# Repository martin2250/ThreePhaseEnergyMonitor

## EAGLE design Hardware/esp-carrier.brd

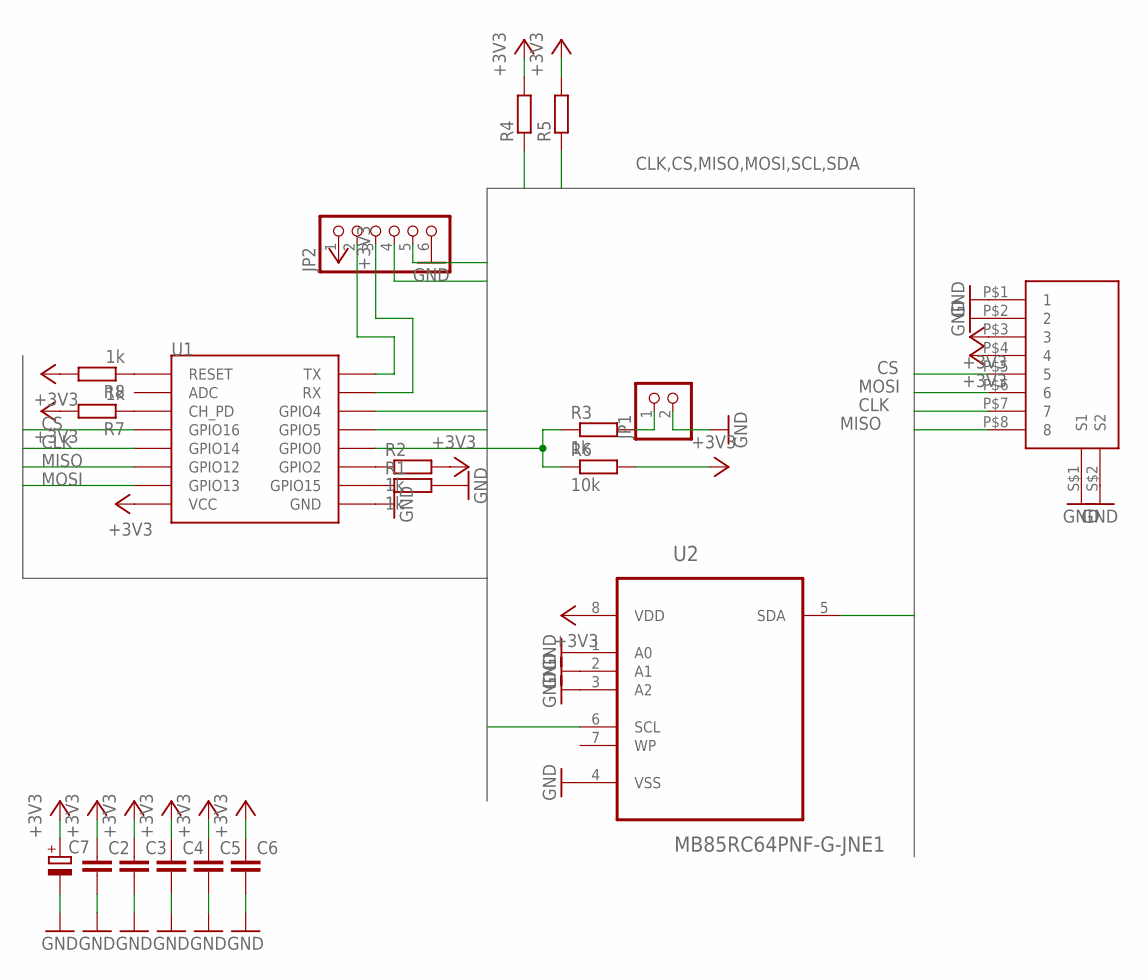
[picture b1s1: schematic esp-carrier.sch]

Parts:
C1: RJ45-ASSMANN
C2, C3, C4, C5, C6: C-EUC0805; C0805
C7: CPOL-EUF; PANASONIC_F
JP1: PINHD-1X2; 1X02
JP2: PINHD-1X6; 1X06
R1, R2, R3, R7, R8: 1k; R0805
R4, R5: R-EU_R0805; R0805
R6: 10k; R0805
U1: ESP12SMD; ESP12-SMD
U2: MB85RC64PNF-G-JNE1; SOIC127P600X175-8N

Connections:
+3V3: C1.P$3 (3), C1.P$4 (4), C2.1, C3.1, C4.1, C5.1, C6.1, C7.+, JP2.1, R2.2, R4.2, R5.2, R6.2, R7.2, R8.2, U1.VCC, U2.8 (VDD)
CLK: C1.P$7 (7), U1.GPIO14
CS: C1.P$5 (5), U1.GPIO16
GND: C1.P$1 (1), C1.P$2 (2), C1.S$1 (S1), C1.S$2 (S2), C2.2, C3.2, C4.2, C5.2, C6.2, C7.-, JP1.2, JP2.6, R1.2, U1.GND, U2.1 (A0), U2.2 (A1), U2.3 (A2), U2.4 (VSS)
MISO: C1.P$8 (8), U1.GPIO12
MOSI: C1.P$6 (6), U1.GPIO13
unnamed: R1.1, U1.GPIO15
unnamed: R2.1, U1.GPIO2
unnamed: R3.1, R6.1, U1.GPIO0
unnamed: JP1.1, R3.2
unnamed: JP2.2, U1.TXD0 (TX)
unnamed: R7.1, U1.CH_PD
unnamed: JP2.3, U1.RXD0 (RX)
unnamed: R8.1, U1.RESET
SCL: JP2.5, R4.1, U1.GPIO5, U2.6 (SCL)
SDA: JP2.4, R5.1, U1.GPIO4, U2.5 (SDA)

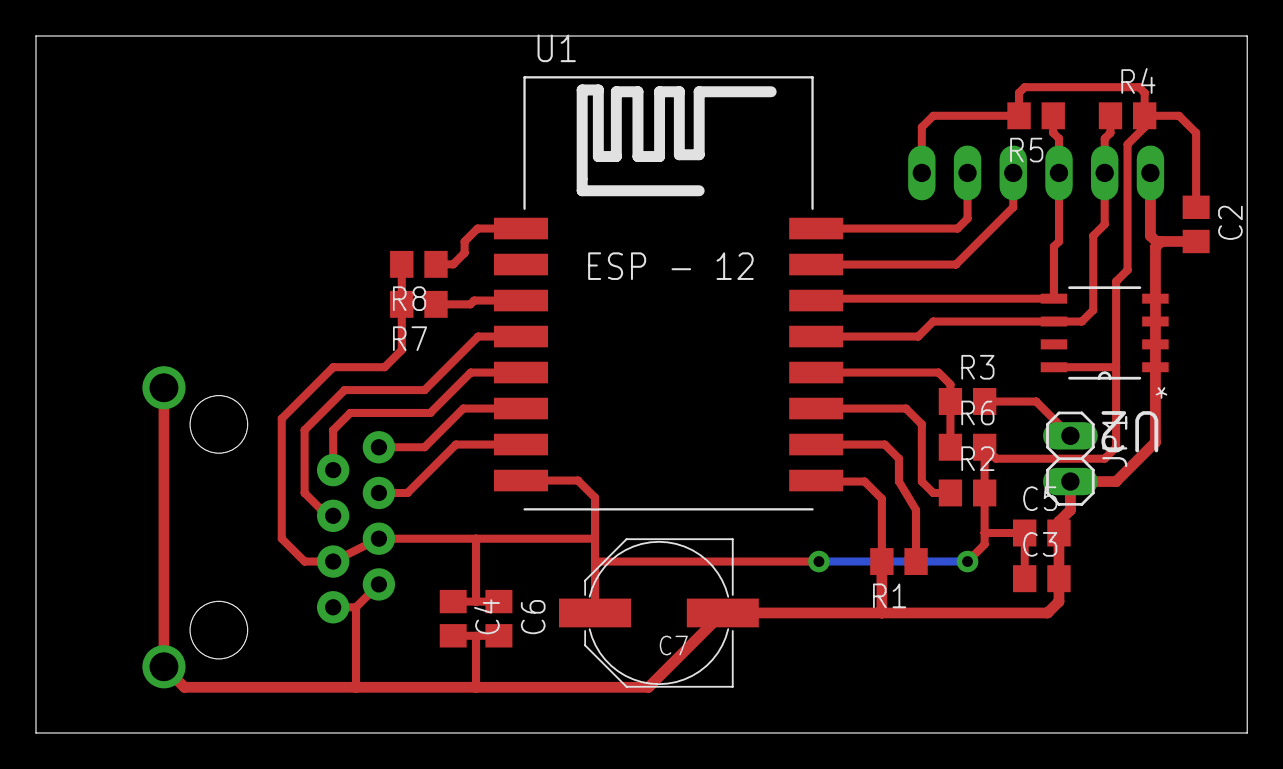
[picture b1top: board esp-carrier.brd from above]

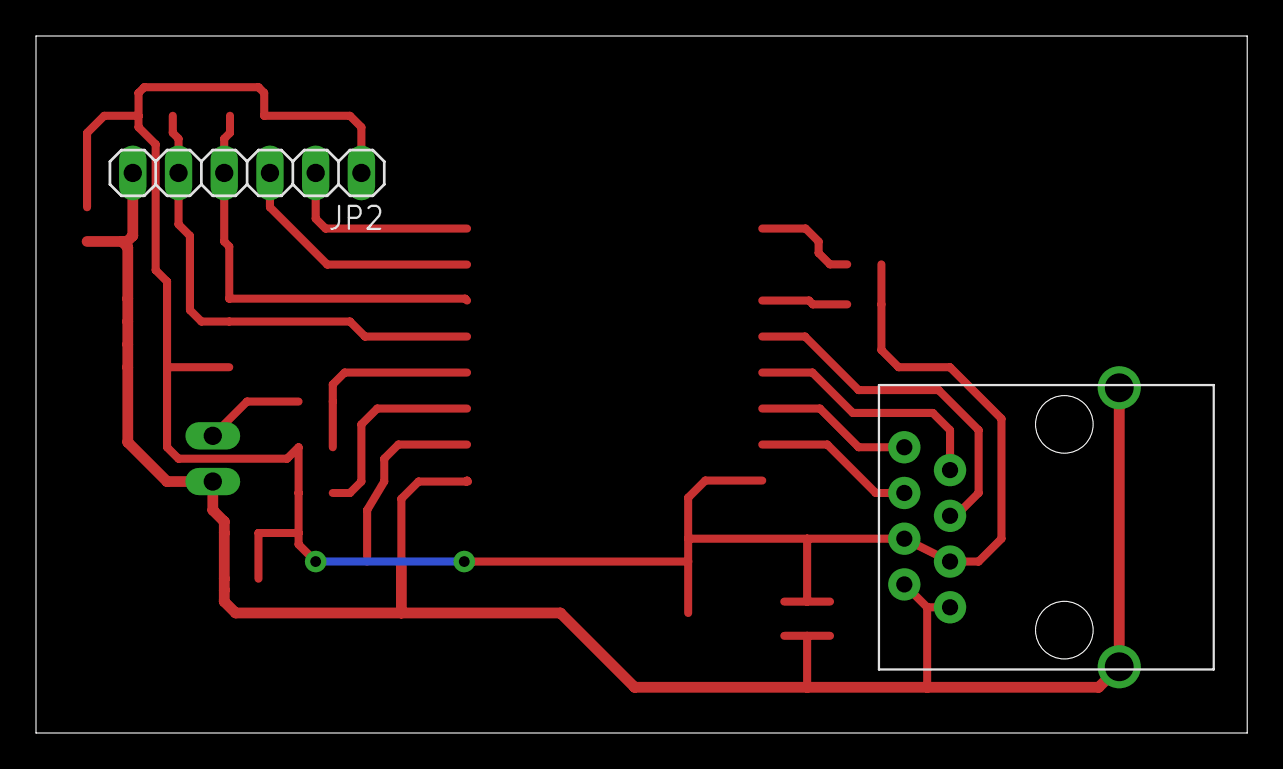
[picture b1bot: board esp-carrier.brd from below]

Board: 2 copper layers, 67.3 x 38.7 mm, 19 parts (2 on the bottom side), 16 nets.

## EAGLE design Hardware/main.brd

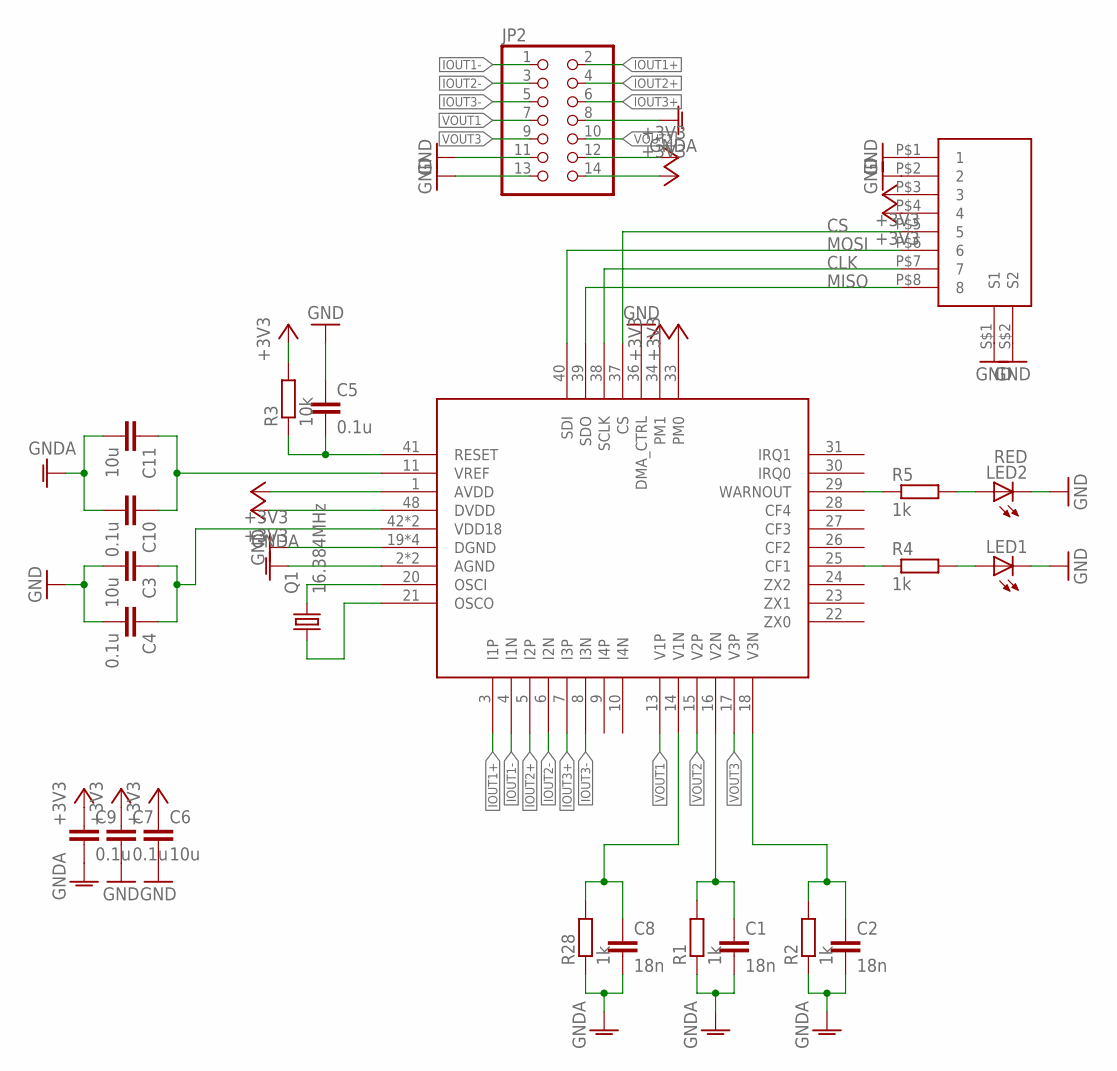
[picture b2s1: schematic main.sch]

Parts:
C1, C2, C8: 18n; C0805
C3, C6: 10u; C1206
C4, C5, C7, C9, C10: 0.1u; C0805
C11: 10u; C0805
C12: RJ45-ASSMANN
JP2: PINHD-2X7; 2X07
LED1: LEDCHIPLED_1206; CHIPLED_1206
LED2: RED; CHIPLED_1206
Q1: 16.384MHz; 5.0X3.2_KX-9A
R1, R2, R28: 1k; M0805
R3: 10k; M0805
R4, R5: 1k; R0805
U$1: ATM90E36A; QFP50P900X900X120-48

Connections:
+3V3: C6.1, C7.1, C9.1, C12.P$3 (3), C12.P$4 (4), JP2.12, JP2.14, R3.2, U$1.1 (AVDD), U$1.33 (PM0), U$1.34 (PM1), U$1.48 (DVDD)
CLK: C12.P$7 (7), U$1.38 (SCLK)
CS: C12.P$5 (5), U$1.37 (CS)
GND: C3.2, C4.2, C5.1, C6.2, C7.2, C12.P$1 (1), C12.P$2 (2), C12.S$1 (S1), C12.S$2 (S2), JP2.11, JP2.13, LED1.C, LED2.C, U$1.19 (DGND), U$1.32 (DGND), U$1.36 (DMA_CTRL), U$1.44 (DGND), U$1.47 (DGND)
GNDA: C1.2, C2.2, C8.2, C9.2, C10.2, C11.2, JP2.8, R1.1, R2.1, R28.1, U$1.2 (AGND), U$1.12 (AGND)
IOUT1+: JP2.2, U$1.3 (I1P)
IOUT1-: JP2.1, U$1.4 (I1N)
IOUT2+: JP2.4, U$1.5 (I2P)
IOUT2-: JP2.3, U$1.6 (I2N)
IOUT3+: JP2.6, U$1.7 (I3P)
IOUT3-: JP2.5, U$1.8 (I3N)
MISO: C12.P$8 (8), U$1.39 (SDO)
MOSI: C12.P$6 (6), U$1.40 (SDI)
unnamed: Q1.3 (2), U$1.20 (OSCI)
unnamed: Q1.1, U$1.21 (OSCO)
unnamed: C5.2, R3.1, U$1.41 (RESET)
unnamed: C3.1, C4.1, U$1.42 (VDD18), U$1.43 (VDD18)
unnamed: R4.1, U$1.25 (CF1)
unnamed: LED1.A, R4.2
unnamed: R5.1, U$1.29 (WARNOUT)
unnamed: LED2.A, R5.2
VOUT1: JP2.7, U$1.13 (V1P)
VOUT2: JP2.10, U$1.15 (V2P)
VOUT3: JP2.9, U$1.17 (V3P)
VOUT4: C8.1, R28.2, U$1.14 (V1N)
VOUT5: C1.1, R1.2, U$1.16 (V2N)
VOUT6: C2.1, R2.2, U$1.18 (V3N)
VREF: C10.1, C11.1, U$1.11 (VREF)

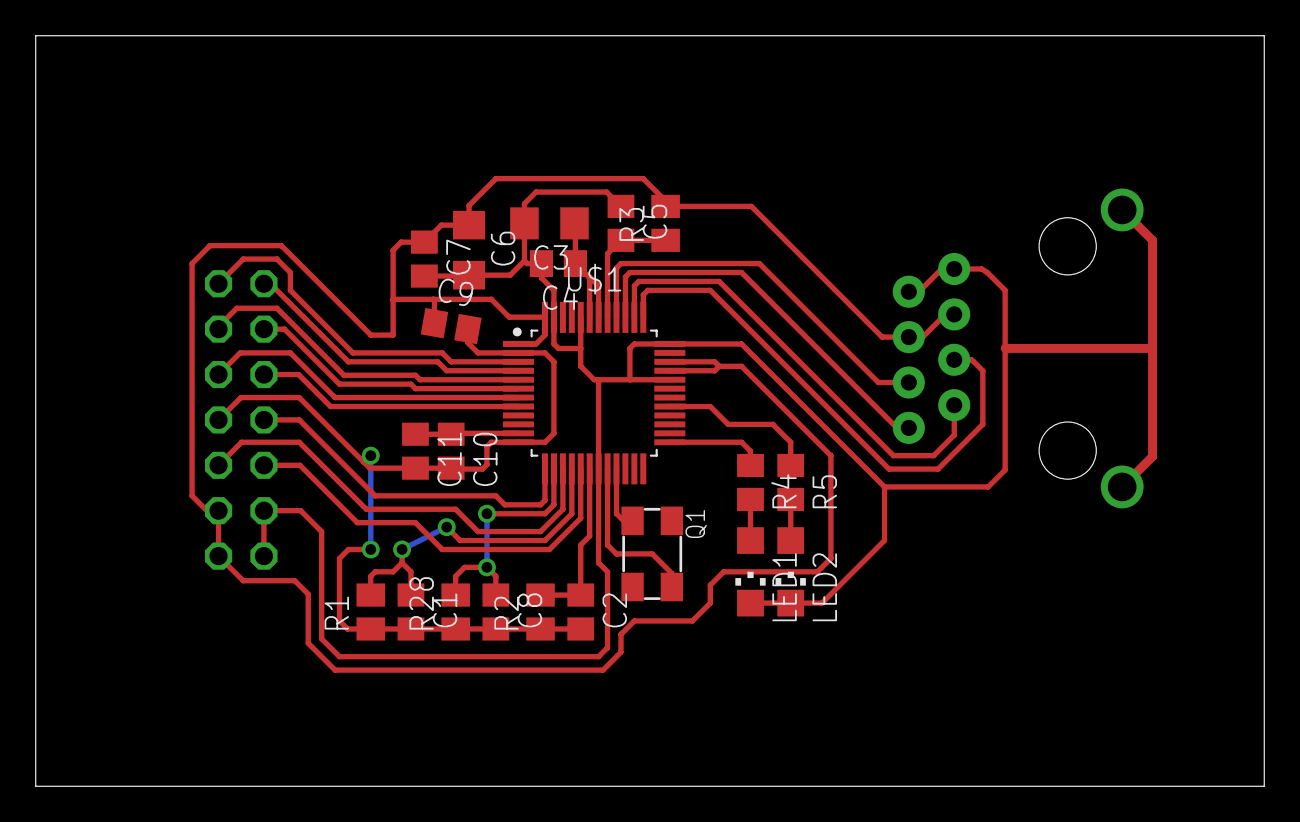
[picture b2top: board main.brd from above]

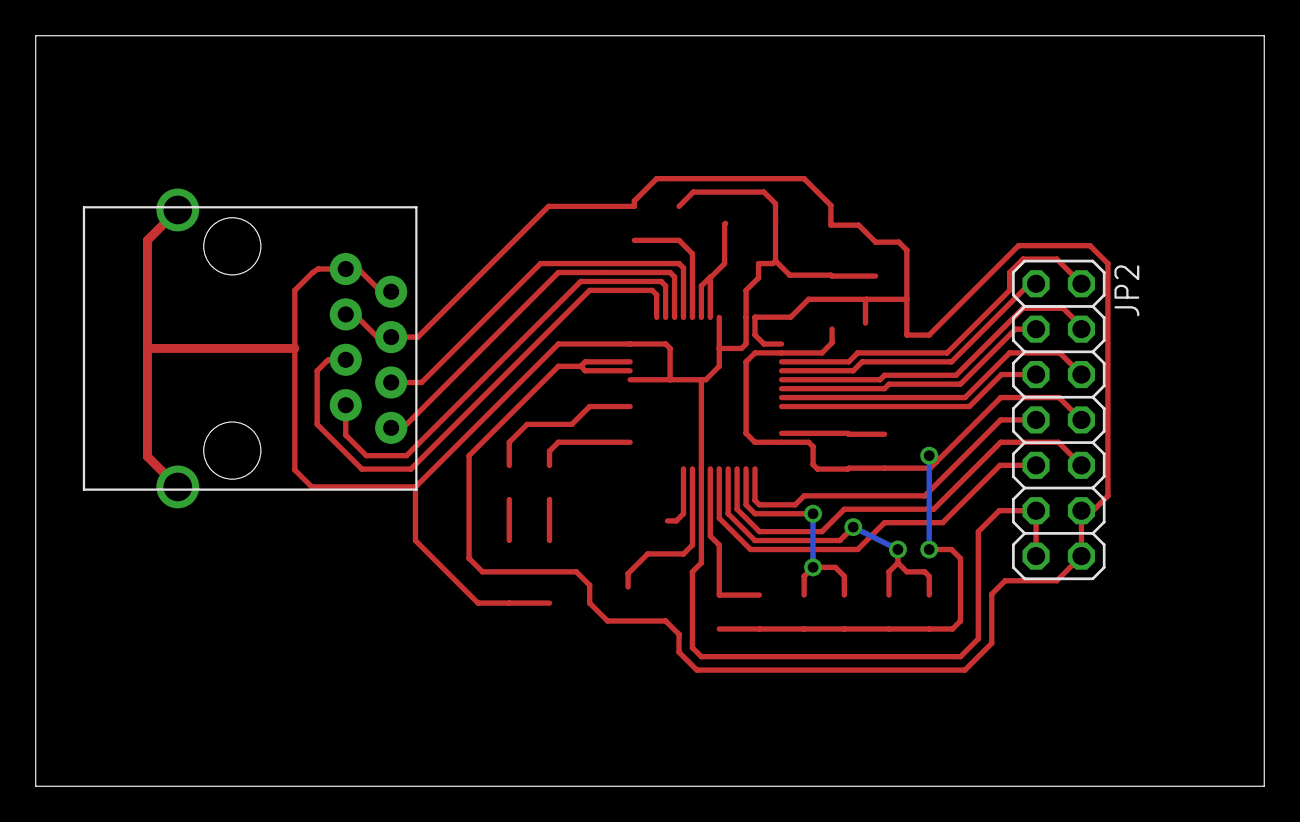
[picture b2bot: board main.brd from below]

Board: 2 copper layers, 68.8 x 42.0 mm, 23 parts (2 on the bottom side), 28 nets.

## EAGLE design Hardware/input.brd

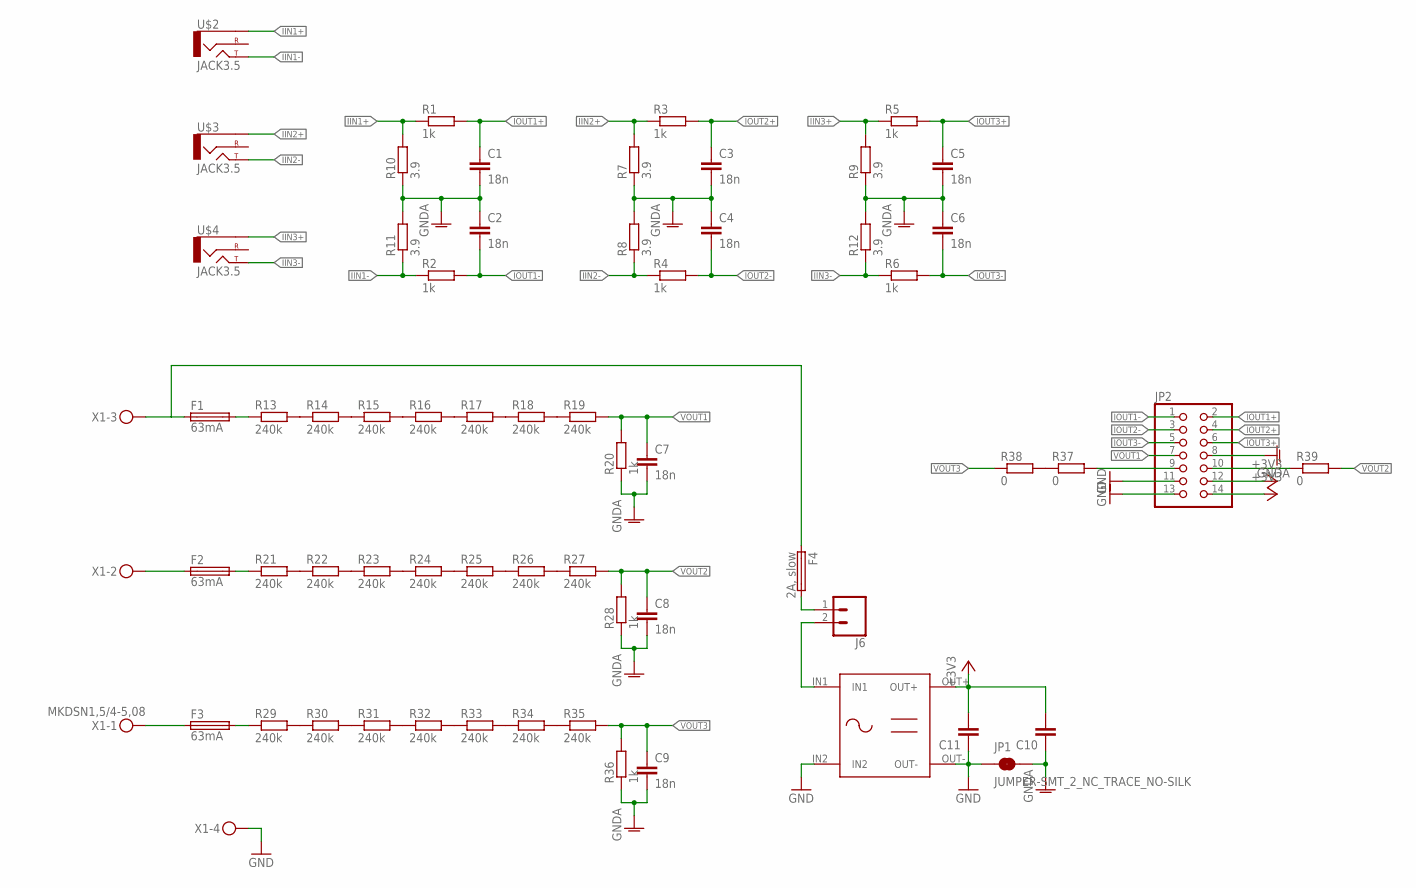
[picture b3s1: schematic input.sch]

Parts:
C1, C2, C3, C4, C5, C6, C7, C8, C9: 18n; C0805
C10, C11: C-EUC1206; C1206
F1, F2, F3: 63mA; SH25
F4: 2A, slow; SH25
J6: CONN_025MM; SCREWTERMINAL-5MM-2
JP1: JUMPER-SMT_2_NC_TRACE_NO-SILK; SMT-JUMPER_2_NC_TRACE_NO-SILK
JP2: PINHD-2X7; 2X07
R1, R2, R3, R4, R5, R6, R20, R28, R36: 1k; M0805
R7, R8, R9, R10, R11, R12: 3.9; M0805
R13, R14, R15, R16, R17, R18, R19, R21, R22, R23, R24, R25, R26, R27, R29, R30, R31, R32, R33, R34, R35: 240k; R1206
R37, R38, R39: 0; R1206
U$1: MW-IRM; MW-IRM-DIP
U$2, U$3, U$4: JACK3.5; AUDIO-JACK
X1: MKDSN1,5/4-5,08

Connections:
+3V3: C10.2, C11.2, JP2.12, JP2.14, U$1.OUT+
GND: C11.1, JP1.1, JP2.11, JP2.13, U$1.IN2, U$1.OUT-, X1.4
GNDA: C1.2, C2.1, C3.2, C4.1, C5.2, C6.1, C7.2, C8.2, C9.2, C10.1, JP1.2, JP2.8, R7.1, R8.2, R9.1, R10.1, R11.2, R12.2, R20.1, R28.1, R36.1
IIN1+: R1.1, R10.2, U$2.SLEEVE
IIN1-: R2.1, R11.1, U$2.TIP
IIN2+: R3.1, R7.2, U$3.SLEEVE
IIN2-: R4.1, R8.1, U$3.TIP
IIN3+: R5.1, R9.2, U$4.SLEEVE
IIN3-: R6.1, R12.1, U$4.TIP
IOUT1+: C1.1, JP2.2, R1.2
IOUT1-: C2.2, JP2.1, R2.2
IOUT2+: C3.1, JP2.4, R3.2
IOUT2-: C4.2, JP2.3, R4.2
IOUT3+: C5.1, JP2.6, R5.2
IOUT3-: C6.2, JP2.5, R6.2
unnamed: R13.2, R14.1
unnamed: R14.2, R15.1
unnamed: R15.2, R16.1
unnamed: R16.2, R17.1
unnamed: R17.2, R18.1
unnamed: R18.2, R19.1
unnamed: F1.1, F4.1, X1.3
unnamed: F4.2, J6.1
unnamed: F3.2, R29.1
unnamed: R21.2, R22.1
unnamed: R22.2, R23.1
unnamed: R23.2, R24.1
unnamed: R25.2, R26.1
unnamed: R26.2, R27.1
unnamed: R24.2, R25.1
unnamed: J6.2, U$1.IN1
unnamed: R29.2, R30.1
unnamed: R30.2, R31.1
unnamed: R31.2, R32.1
unnamed: R33.2, R34.1
unnamed: R34.2, R35.1
unnamed: R32.2, R33.1
unnamed: R37.1, R38.2
unnamed: F1.2, R13.1
unnamed: F2.1, X1.2
unnamed: JP2.10, R39.1
unnamed: F2.2, R21.1
unnamed: JP2.9, R37.2
unnamed: F3.1, X1.1
VOUT1: C7.1, JP2.7, R19.2, R20.2
VOUT2: C8.1, R27.2, R28.2, R39.2
VOUT3: C9.1, R35.2, R36.2, R38.1

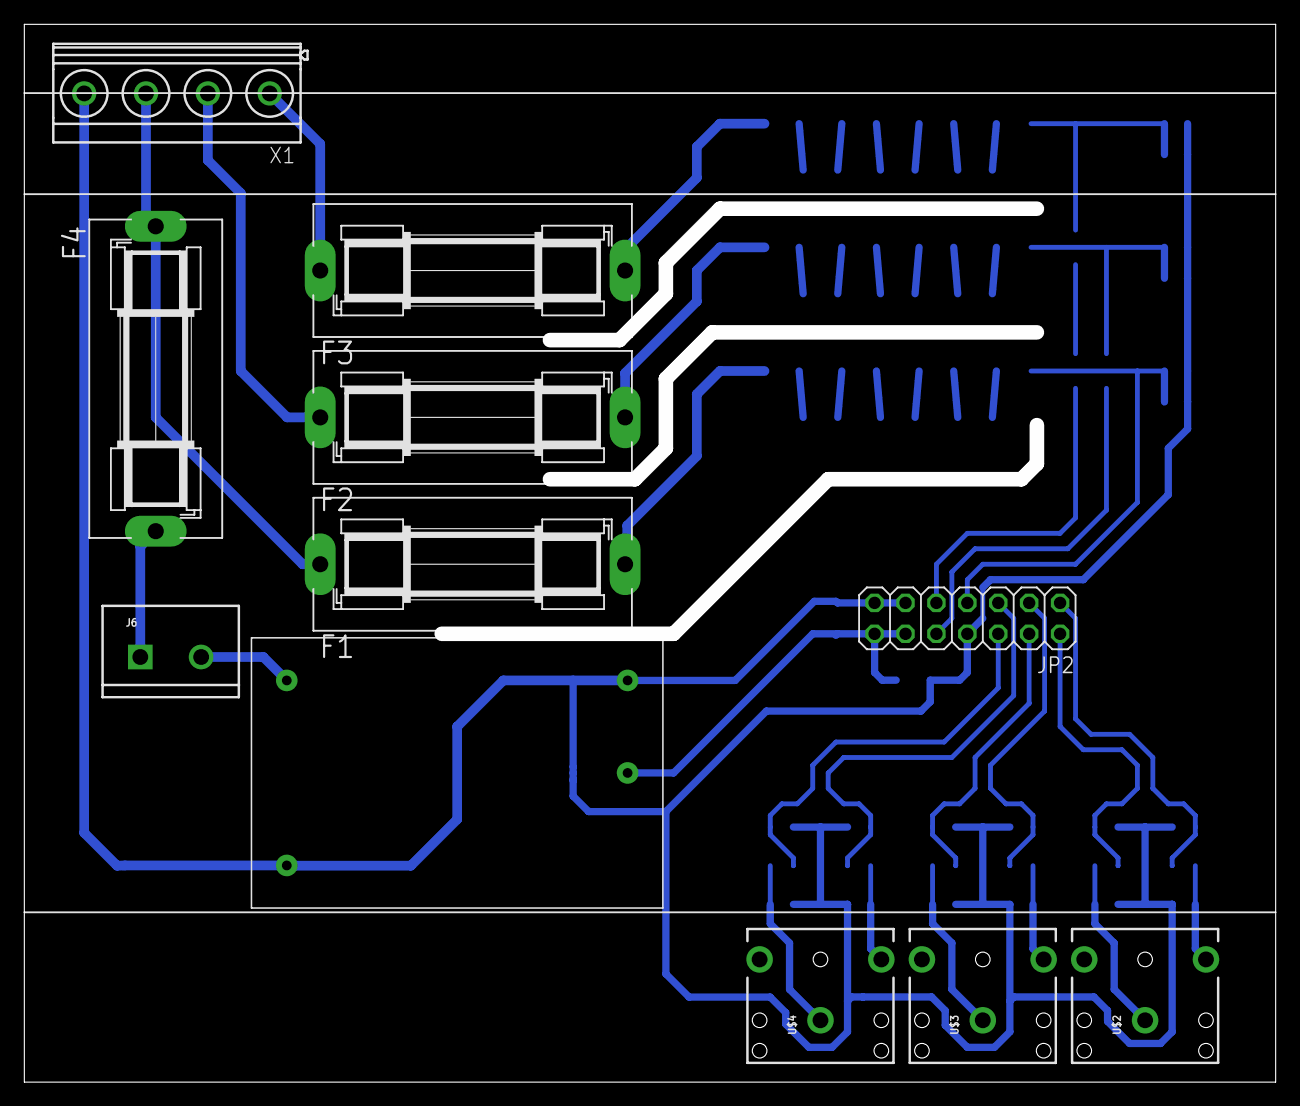
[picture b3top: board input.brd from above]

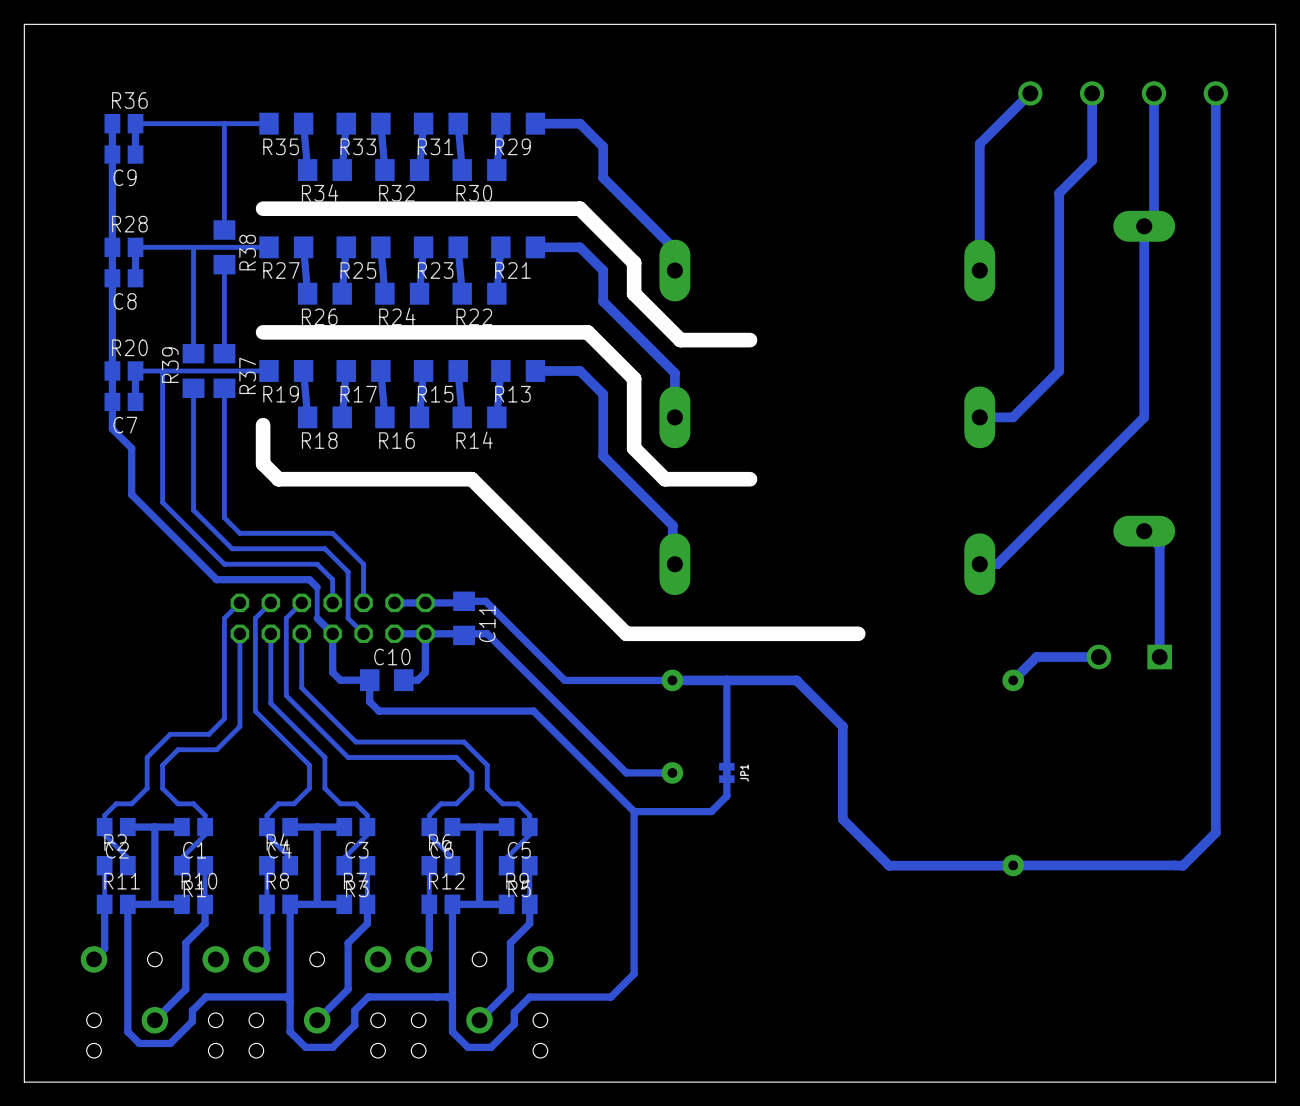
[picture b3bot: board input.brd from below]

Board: 2 copper layers, 101.6 x 85.7 mm, 62 parts (51 on the bottom side), 47 nets.

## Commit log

2019-06-22 improve metric pusher untested
2019-06-22 add timeout to push client
2019-06-23 change ip to pi
2019-09-01 update for minitsdb
2019-09-02 hopefully fix lost connections
2019-09-04 add upd sender

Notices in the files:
parts and their libraries:
SparkFun-Connectors: Licensing: Creative Commons ShareAlike 4.0 International - https://creativecommons.org/licenses/by-sa/4.0
crystal-geyer_V1_0: Copyright: Geyer-Electronic
